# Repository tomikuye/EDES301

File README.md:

# EDES301
 <p>Repository for EDES301 course work</p>

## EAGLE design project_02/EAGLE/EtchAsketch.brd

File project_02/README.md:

# EDES301
 <p>EtchASketch PCB</p>

This is a custom PCB created for a EDES 301 project to replicate the classic Etch-A-Sketch toy using analog potentiometers, pushbuttons, and an LCD screen. The board is designed to interface with a PocketBeagle for control and rendering.

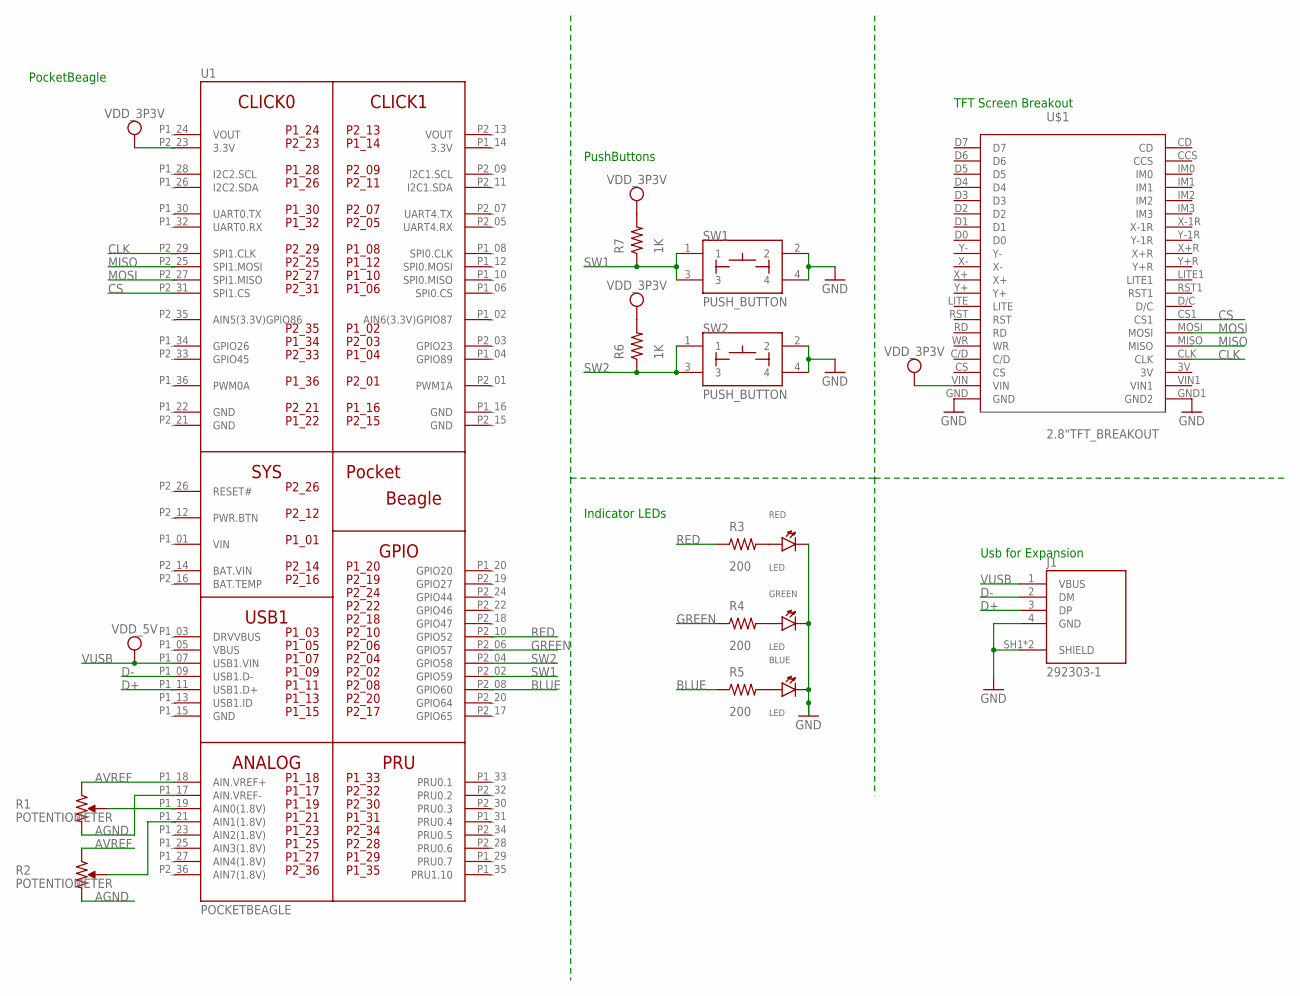
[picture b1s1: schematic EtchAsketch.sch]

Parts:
BLUE: LED; EIA-STD
GREEN: LED; EIA-STD
J1: 292303-1; TE_292303-1
R1, R2: POTENTIOMETER; POT-PO90S
R3, R4, R5: 200; R0402
R6, R7: 1K; R0402
RED: LED; EIA-STD
SW1, SW2: PUSH_BUTTON; BUTTON_12.5MM
U1: POCKETBEAGLE
U$1: 2.8"TFT_BREAKOUT; 2.8"TFTBRTEAKOUT

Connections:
3.3V: U1.P1_14 (3.3V)
AGND: R1.CW, R2.CW, U1.P1_17 (AIN.VREF-)
AVREF: R1.CCW, R2.CCW, U1.P1_18 (AIN.VREF+)
BAT.VIN: U1.P2_14 (BAT.VIN)
BLUE: R5.1, U1.P2_08 (GPIO60)
CLK: U1.P2_29 (SPI1.CLK), U$1.CLK
CS: U1.P2_31 (SPI1.CS), U$1.CS1
D+: J1.3 (DP), U1.P1_11 (USB1.D+)
D-: J1.2 (DM), U1.P1_09 (USB1.D-)
GND: BLUE.CATHODE, GREEN.CATHODE, J1.4 (GND), J1.SH1 (SHIELD), J1.SH2 (SHIELD), RED.CATHODE, SW1.2, SW1.4, SW2.2, SW2.4, U1.P1_16 (GND), U1.P1_22 (GND), U1.P2_15 (GND), U1.P2_21 (GND), U$1.GND, U$1.GND1 (GND2)
GREEN: R4.1, U1.P2_06 (GPIO57)
MISO: U1.P2_25 (SPI1.MOSI), U$1.MISO
MOSI: U1.P2_27 (SPI1.MISO), U$1.MOSI
unnamed: R3.2, RED.ANODE
unnamed: R1.S, U1.P1_19 (AIN0(1.8V))
unnamed: GREEN.ANODE, R4.2
unnamed: BLUE.ANODE, R5.2
unnamed: R2.S, U1.P1_21 (AIN1(1.8V))
RED: R3.1, U1.P2_10 (GPIO52)
SW1: R7.1, SW1.1, SW1.3, U1.P2_02 (GPIO59)
SW2: R6.1, SW2.1, SW2.3, U1.P2_04 (GPIO58)
VDD_3P3V: R6.2, R7.2, U1.P2_23 (3.3V), U$1.VIN
VIN: U1.P1_01 (VIN)
VOUT: U1.P1_24 (VOUT), U1.P2_13 (VOUT)
VUSB: J1.1 (VBUS), U1.P1_07 (USB1.VIN)

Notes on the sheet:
PushButtons
Usb for Expansion
TFT Screen Breakout
PocketBeagle
Indicator LEDs

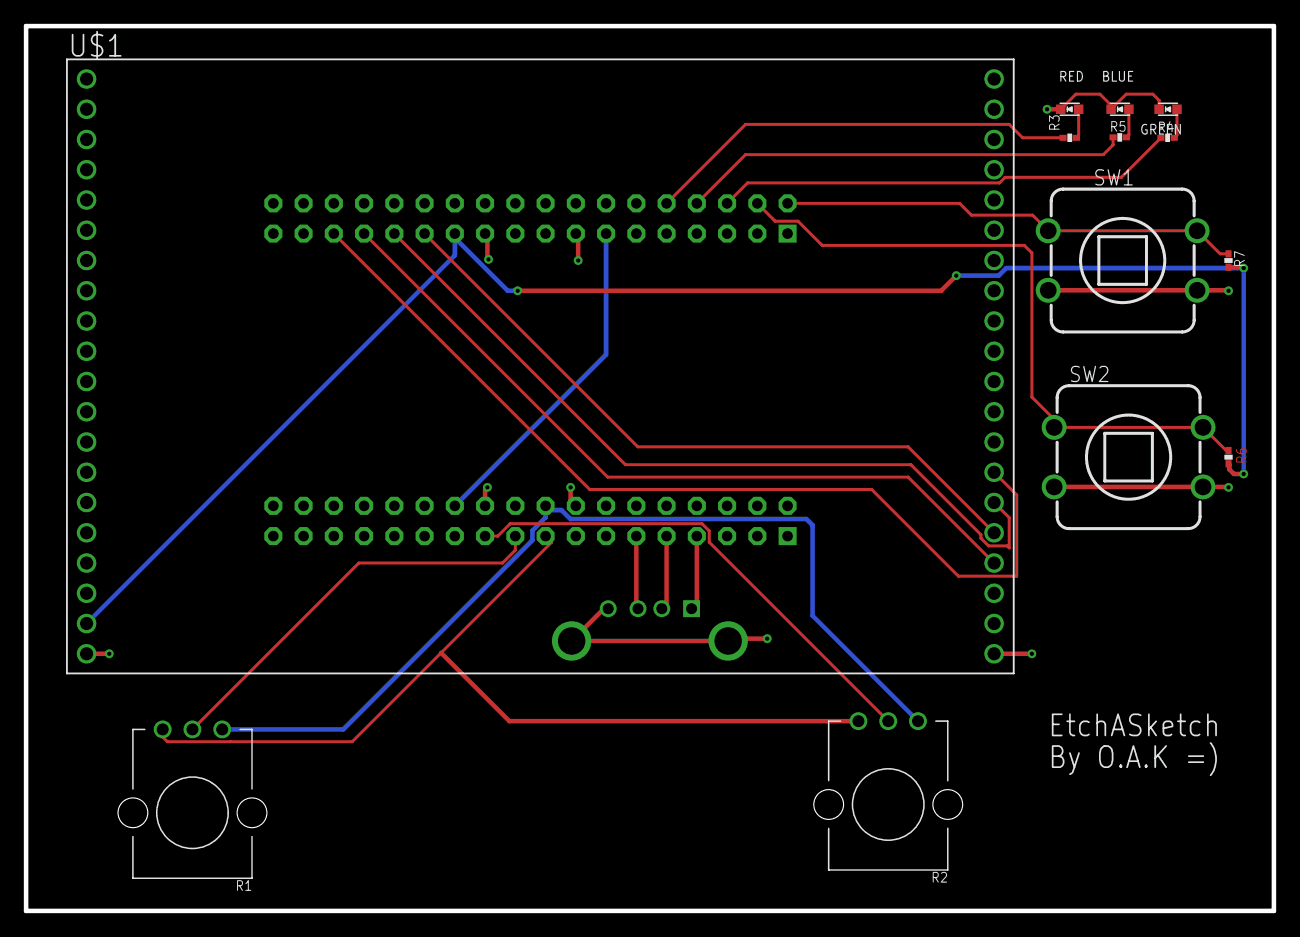
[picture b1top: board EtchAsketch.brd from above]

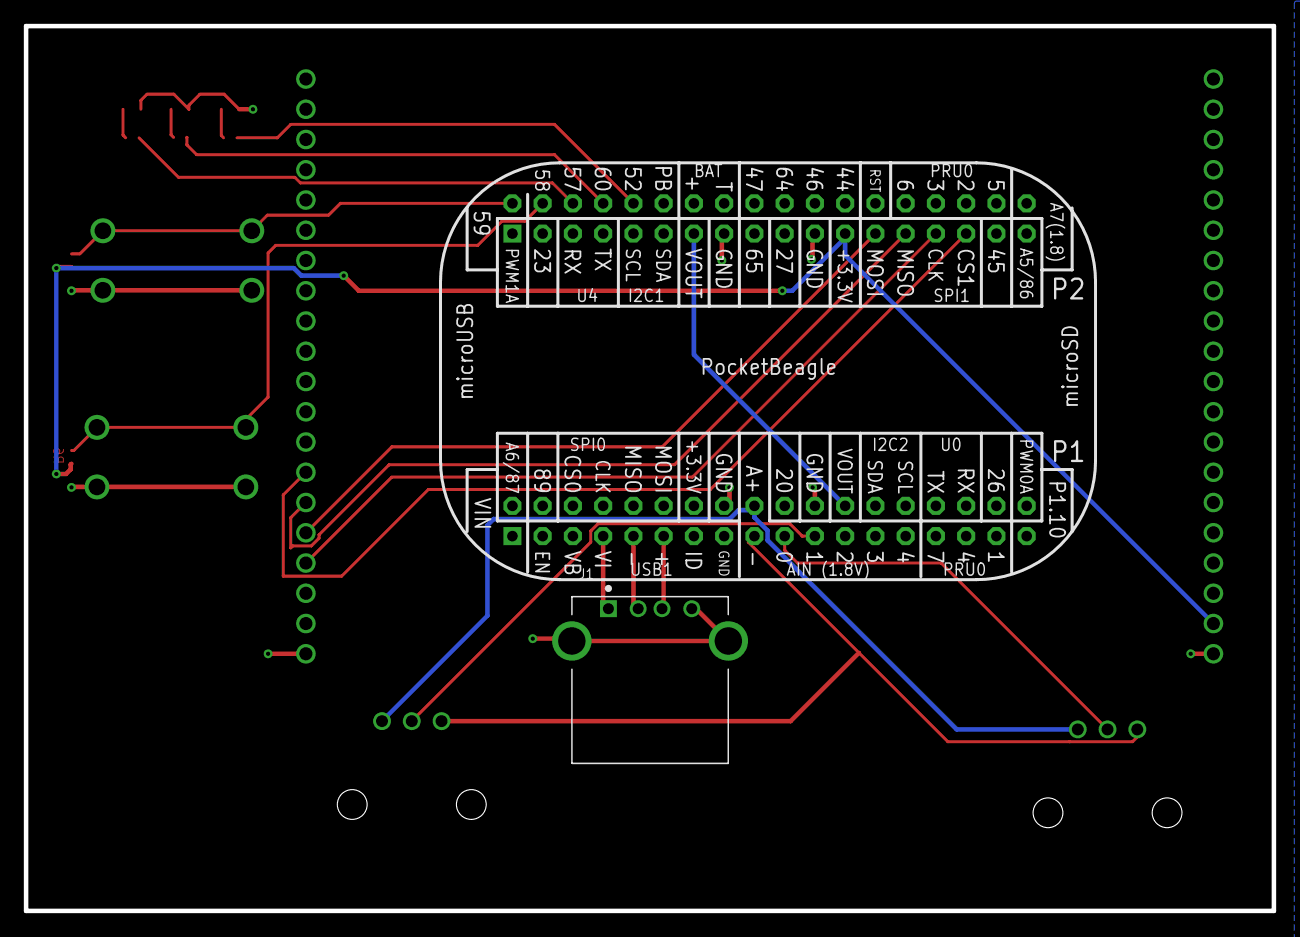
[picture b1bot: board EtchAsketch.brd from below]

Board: 2 copper layers, 104.8 x 74.3 mm, 15 parts (2 on the bottom side), 22 nets.

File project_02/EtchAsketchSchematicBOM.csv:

"Qty";"Value";"Device";"Footprint Name";"Parts";"Detailed Description";"";
"2";"1K";"R_R0402";"R0402";"R6, R7";"RESISTOR, American symbol";"";
"1";"2.8"TFT_BREAKOUT";"2.8"TFT_BREAKOUT";"2.8"TFTBRTEAKOUT";"U$1";"";"";
"3";"200";"R_R0402";"R0402";"R3, R4, R5";"RESISTOR, American symbol";"";
"1";"292303-1";"292303-1";"TE_292303-1";"J1";"CONN USB RECEPT R/A TYPE A 4POS Check availability";"";
"3";"LED";"LED";"EIA-STD";"BLUE, GREEN, RED";"EIA-STD LED, LTST-C191TBKT";"";
"1";"POCKETBEAGLE";"POCKETBEAGLE";"POCKETBEAGLE";"U1";"";"";
"2";"POTENTIOMETER";"POTENTIOMETER";"POT-PO90S";"R1, R2";"Potentiometer - Examples:";"";
"2";"PUSH_BUTTON";"PUSH_BUTTON";"BUTTON_12.5MM";"SW1, SW2";"";"";

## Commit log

2025-02-19 Assignment 4 commits
2025-02-24 Project 1 init
2025-05-06 Init Project 2
2025-05-06 Project 2
2025-05-06 Project 1 updatyes
